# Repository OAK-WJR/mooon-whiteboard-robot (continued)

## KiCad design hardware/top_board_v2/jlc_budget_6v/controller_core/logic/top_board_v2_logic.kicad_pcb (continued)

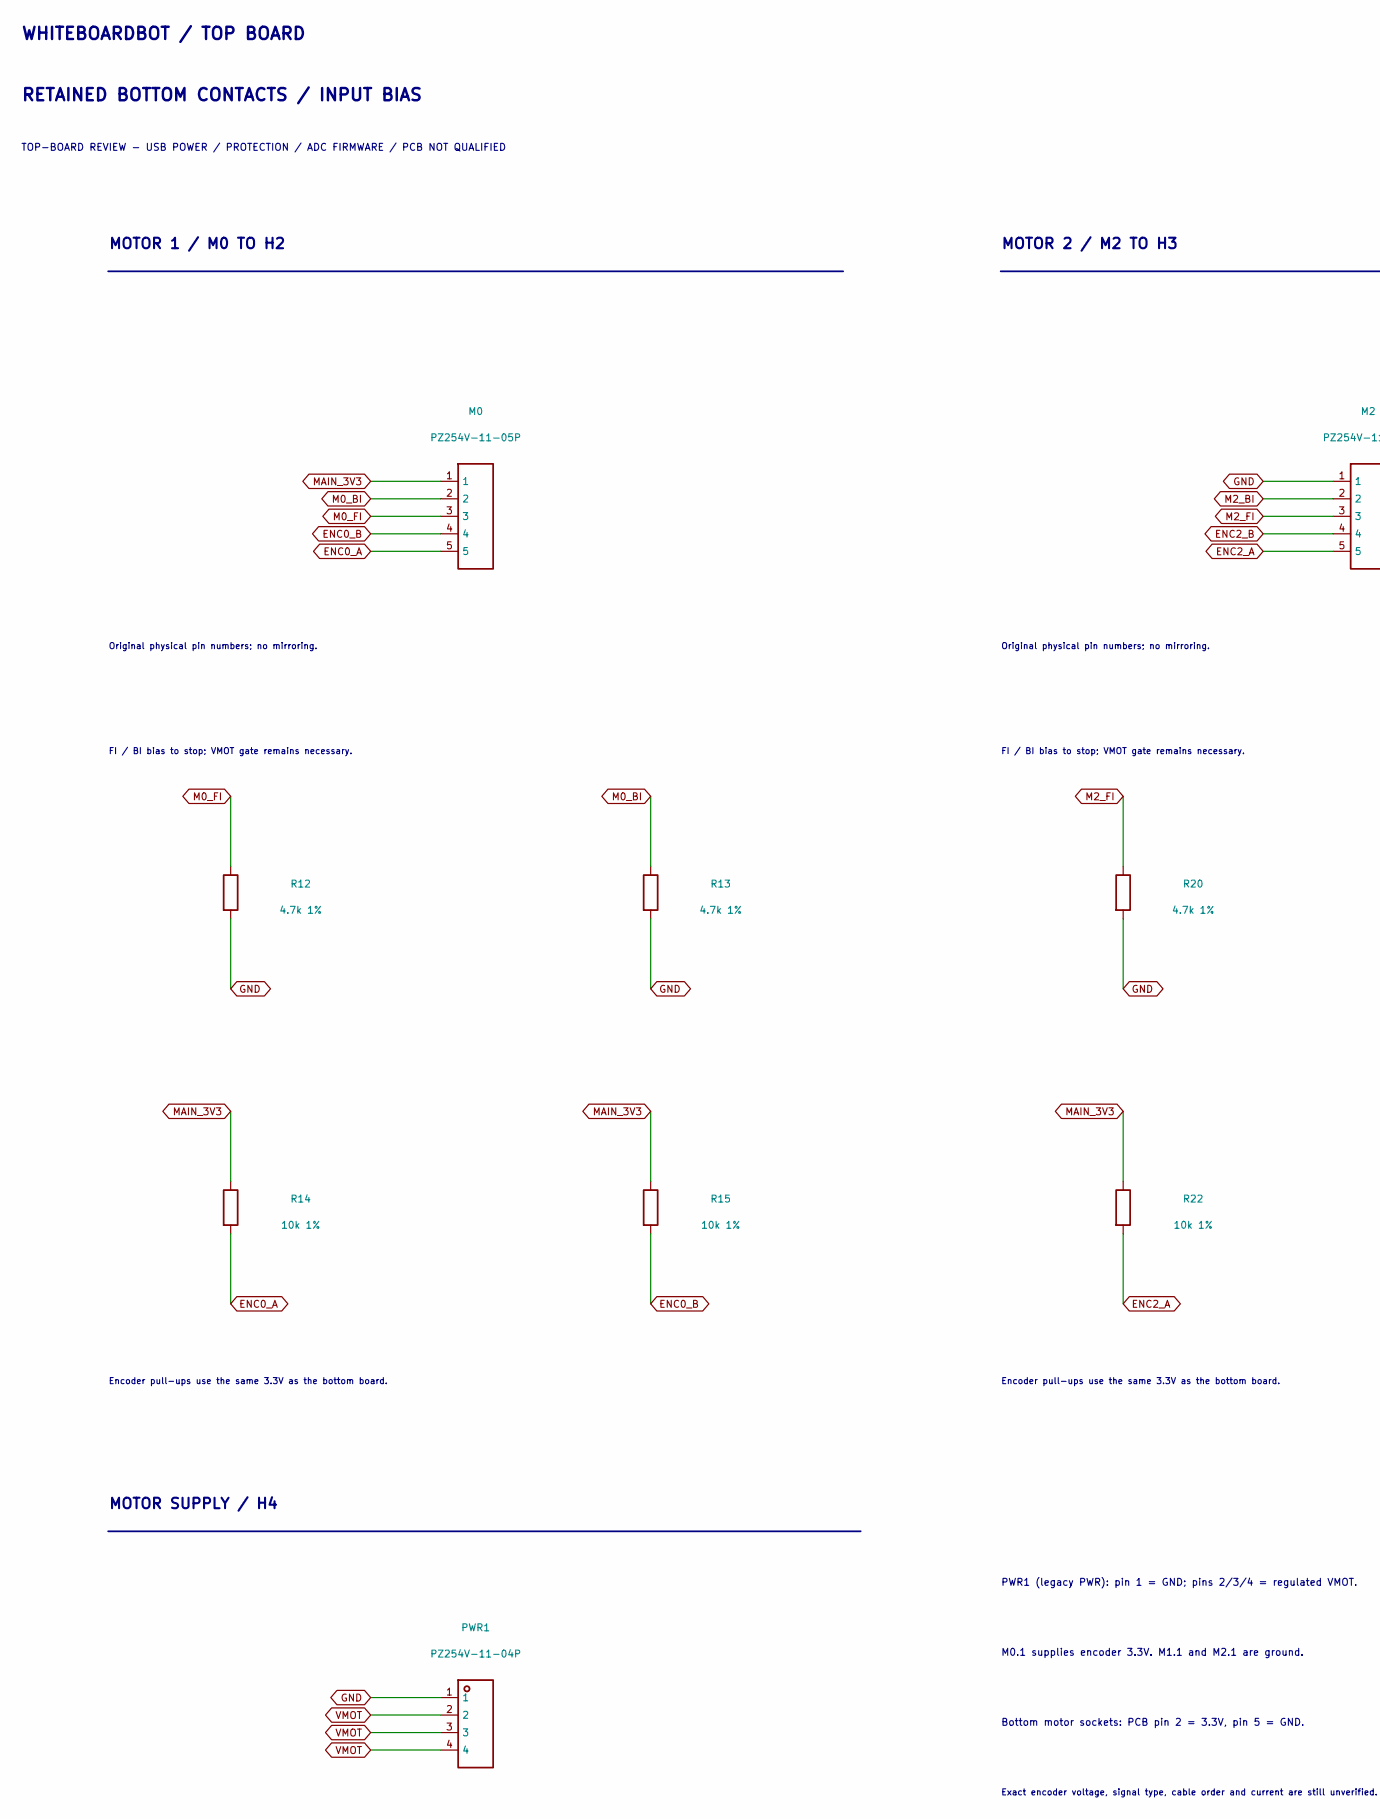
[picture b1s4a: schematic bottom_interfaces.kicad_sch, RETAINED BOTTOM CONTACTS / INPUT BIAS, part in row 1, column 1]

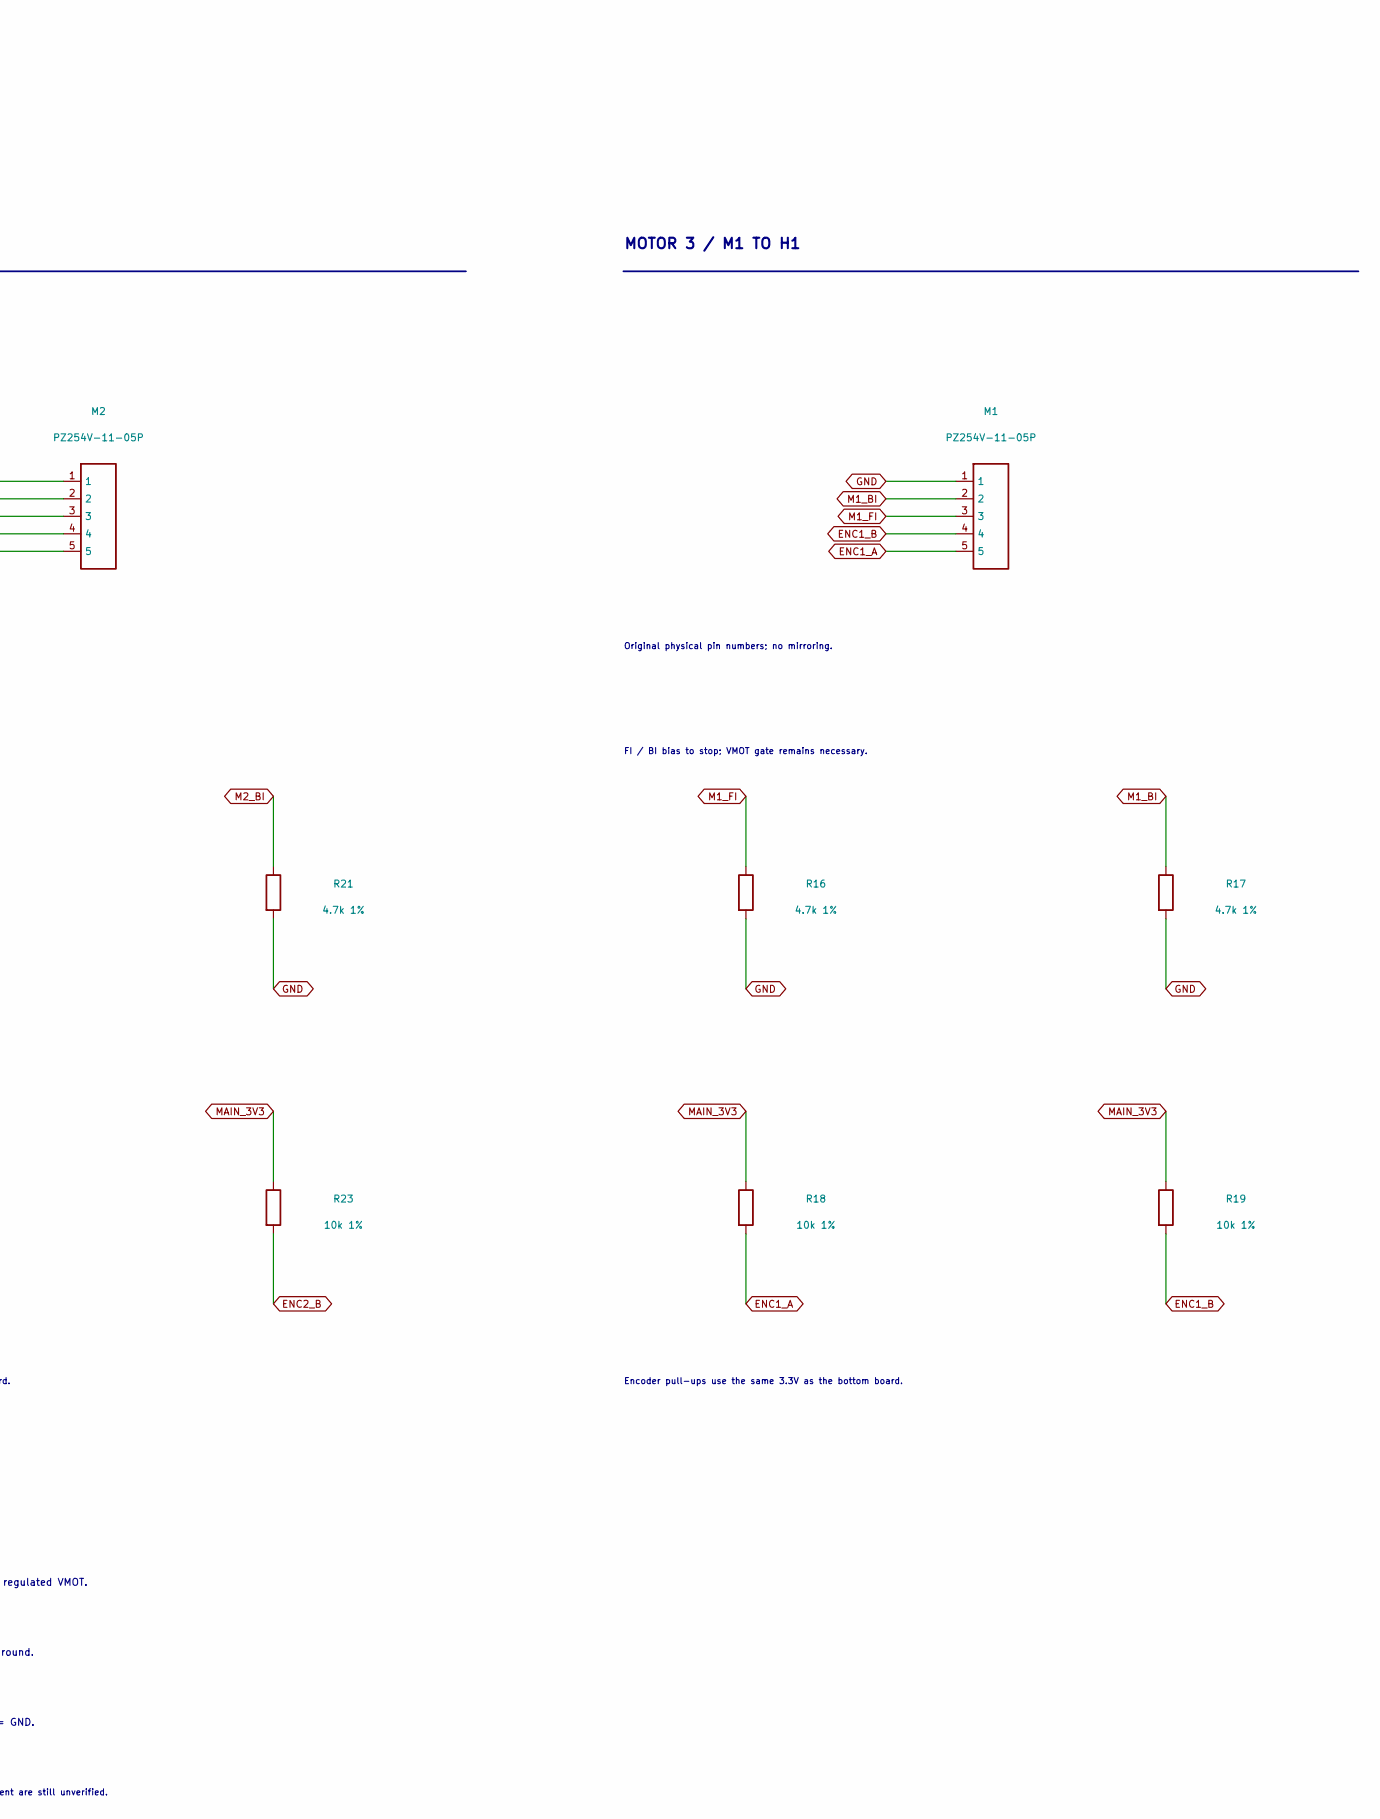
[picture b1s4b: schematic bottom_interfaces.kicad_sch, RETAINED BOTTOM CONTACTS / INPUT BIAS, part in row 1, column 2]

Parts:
M0: PZ254V-11-05P; M0_HDR-TH_5P-P2.54-V-M; LCSC C492404
M1: PZ254V-11-05P; M1_HDR-TH_5P-P2.54-V-M; LCSC C492404
M2: PZ254V-11-05P; M2_HDR-TH_5P-P2.54-V-M; LCSC C492404
PWR1: PZ254V-11-04P; PWR_HDR-TH_4P-P2.54-V-M; LCSC C2691448
R12, R13, R16, R17, R20, R21: 4.7k 1%; R_0603_1608Metric; mpn 0603WAF4701T5E; LCSC C23162
R14, R15, R18, R19, R22, R23: 10k 1%; R_0603_1608Metric; mpn 0603WAF1002T5E; LCSC C25804

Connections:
ENC0_A: M0.5, R14.2; also elsewhere on the board
ENC0_B: M0.4, R15.2; also elsewhere on the board
ENC1_A: M1.5, R18.2; also elsewhere on the board
ENC1_B: M1.4, R19.2; also elsewhere on the board
ENC2_A: M2.5, R22.2; also elsewhere on the board
ENC2_B: M2.4, R23.2; also elsewhere on the board
GND: M1.1, M2.1, PWR1.1, R12.2, R13.2, R16.2, R17.2, R20.2, R21.2; also elsewhere on the board
M0_BI: M0.2, R13.1; also elsewhere on the board
M0_FI: M0.3, R12.1; also elsewhere on the board
M1_BI: M1.2, R17.1; also elsewhere on the board
M1_FI: M1.3, R16.1; also elsewhere on the board
M2_BI: M2.2, R21.1; also elsewhere on the board
M2_FI: M2.3, R20.1; also elsewhere on the board
MAIN_3V3: M0.1, R14.1, R15.1, R18.1, R19.1, R22.1, R23.1; also elsewhere on the board
VMOT: PWR1.2, PWR1.3, PWR1.4; also elsewhere on the board

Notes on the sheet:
WHITEBOARDBOT / TOP BOARD
RETAINED BOTTOM CONTACTS / INPUT BIAS
TOP-BOARD REVIEW - USB POWER / PROTECTION / ADC FIRMWARE / PCB NOT QUALIFIED
MOTOR 1 / M0 TO H2
Original physical pin numbers; no mirroring.
FI / BI bias to stop; VMOT gate remains necessary.
Encoder pull-ups use the same 3.3V as the bottom board.
MOTOR 2 / M2 TO H3
MOTOR 3 / M1 TO H1
MOTOR SUPPLY / H4
PWR1 (legacy PWR): pin 1 = GND; pins 2/3/4 = regulated VMOT.
M0.1 supplies encoder 3.3V. M1.1 and M2.1 are ground.
Bottom motor sockets: PCB pin 2 = 3.3V, pin 5 = GND.
Exact encoder voltage, signal type, cable order and current are still unverified.

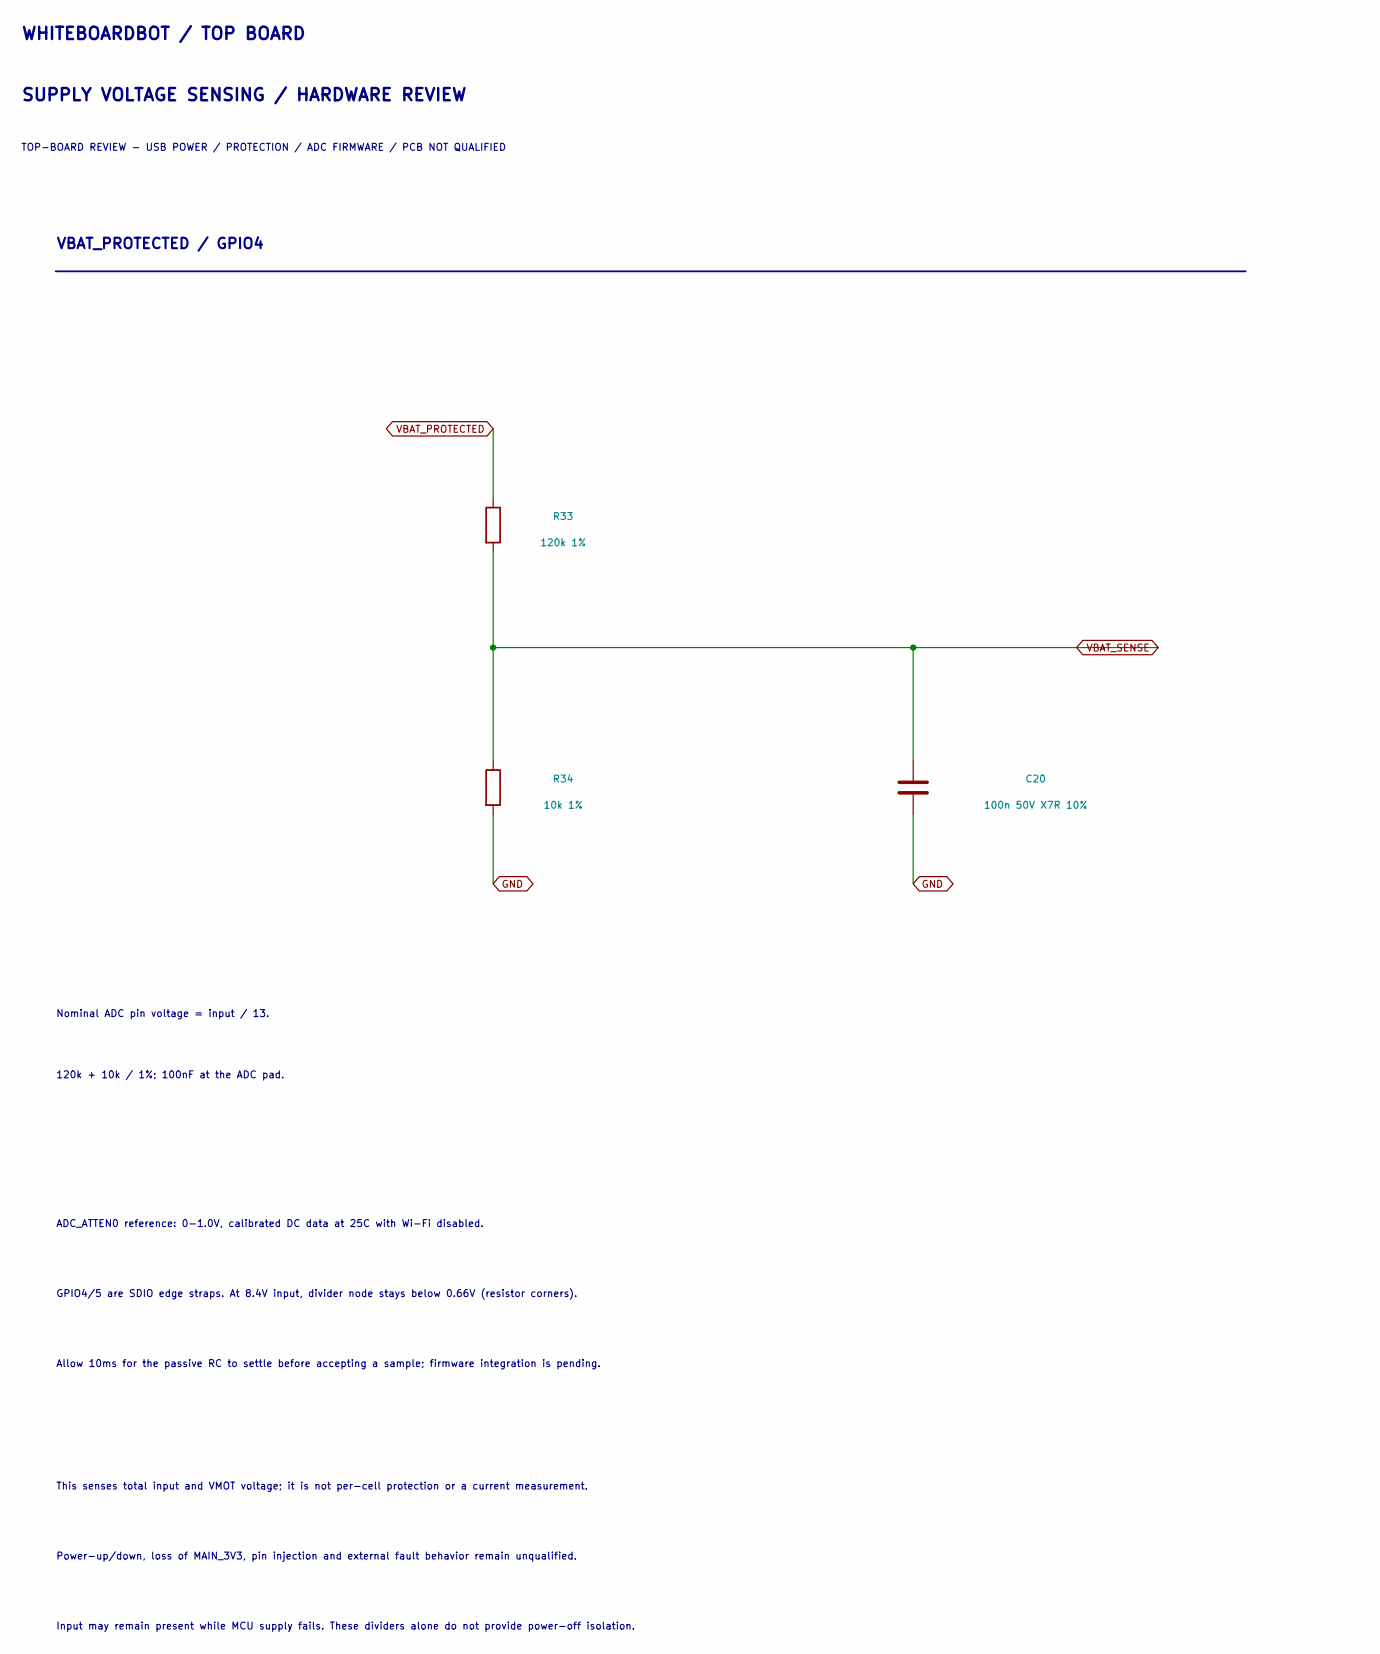
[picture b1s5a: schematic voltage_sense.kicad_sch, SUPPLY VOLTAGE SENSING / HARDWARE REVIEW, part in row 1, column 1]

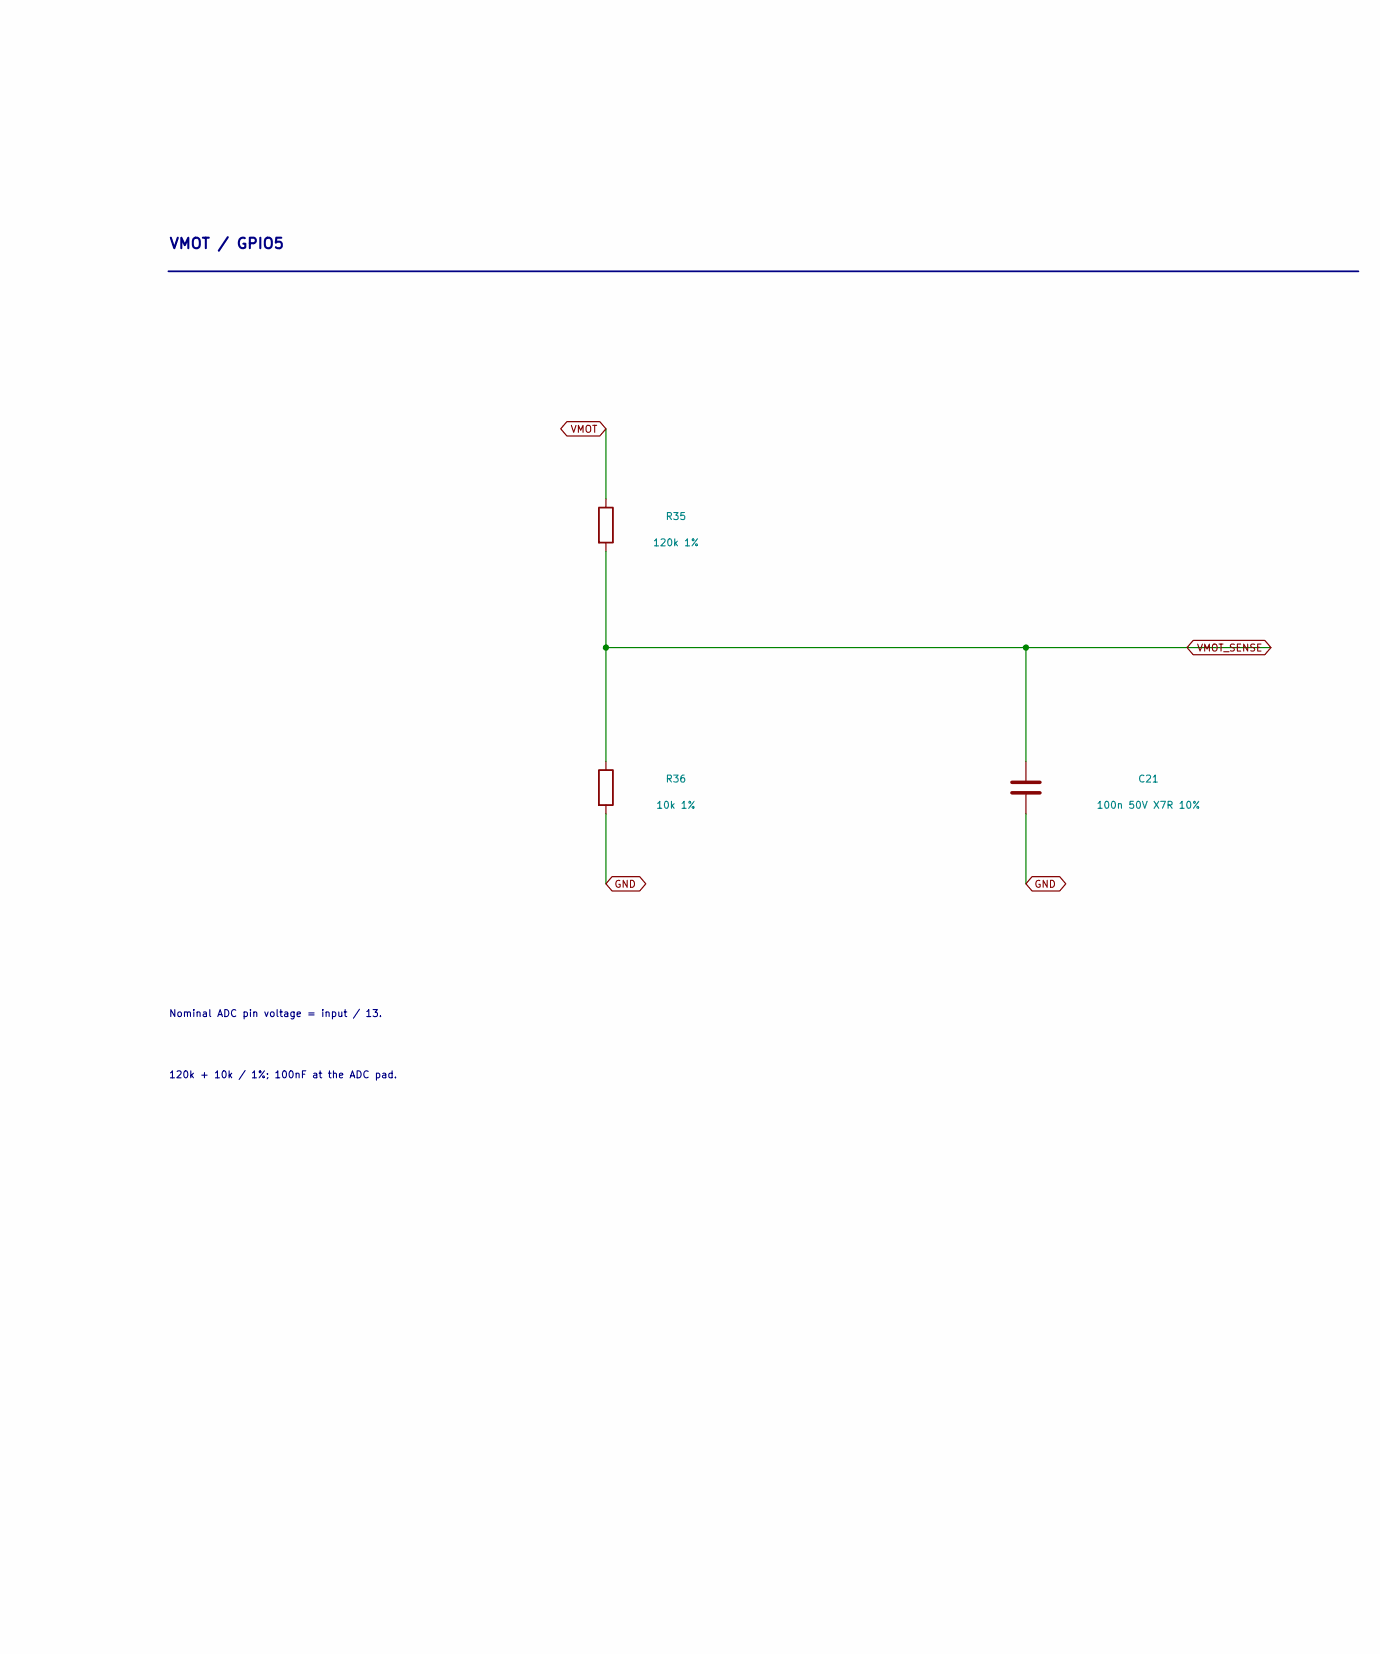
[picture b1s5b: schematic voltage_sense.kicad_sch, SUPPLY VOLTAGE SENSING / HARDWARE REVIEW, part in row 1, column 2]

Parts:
C20, C21: 100n 50V X7R 10%; C_0603_1608Metric; mpn CC0603KRX7R9BB104; LCSC C14663
R33, R35: 120k 1%; R_0603_1608Metric; mpn 0603WAF1203T5E; LCSC C25808
R34, R36: 10k 1%; R_0603_1608Metric; mpn 0603WAF1002T5E; LCSC C25804

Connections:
GND: C20.2, C21.2, R34.2, R36.2; also elsewhere on the board
VBAT_PROTECTED: R33.1; also elsewhere on the board
VBAT_SENSE: C20.1, R33.2, R34.1; also elsewhere on the board
VMOT: R35.1; also elsewhere on the board
VMOT_SENSE: C21.1, R35.2, R36.1; also elsewhere on the board

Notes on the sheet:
WHITEBOARDBOT / TOP BOARD
SUPPLY VOLTAGE SENSING / HARDWARE REVIEW
TOP-BOARD REVIEW - USB POWER / PROTECTION / ADC FIRMWARE / PCB NOT QUALIFIED
VBAT_PROTECTED / GPIO4
Nominal ADC pin voltage = input / 13.
120k + 10k / 1%; 100nF at the ADC pad.
VMOT / GPIO5
ADC_ATTEN0 reference: 0-1.0V, calibrated DC data at 25C with Wi-Fi disabled.
GPIO4/5 are SDIO edge straps. At 8.4V input, divider node stays below 0.66V (resistor corners).
Allow 10ms for the passive RC to settle before accepting a sample; firmware integration is pending.
This senses total input and VMOT voltage; it is not per-cell protection or a current measurement.
Power-up/down, loss of MAIN_3V3, pin injection and external fault behavior remain unqualified.
Input may remain present while MCU supply fails. These dividers alone do not provide power-off isolation.

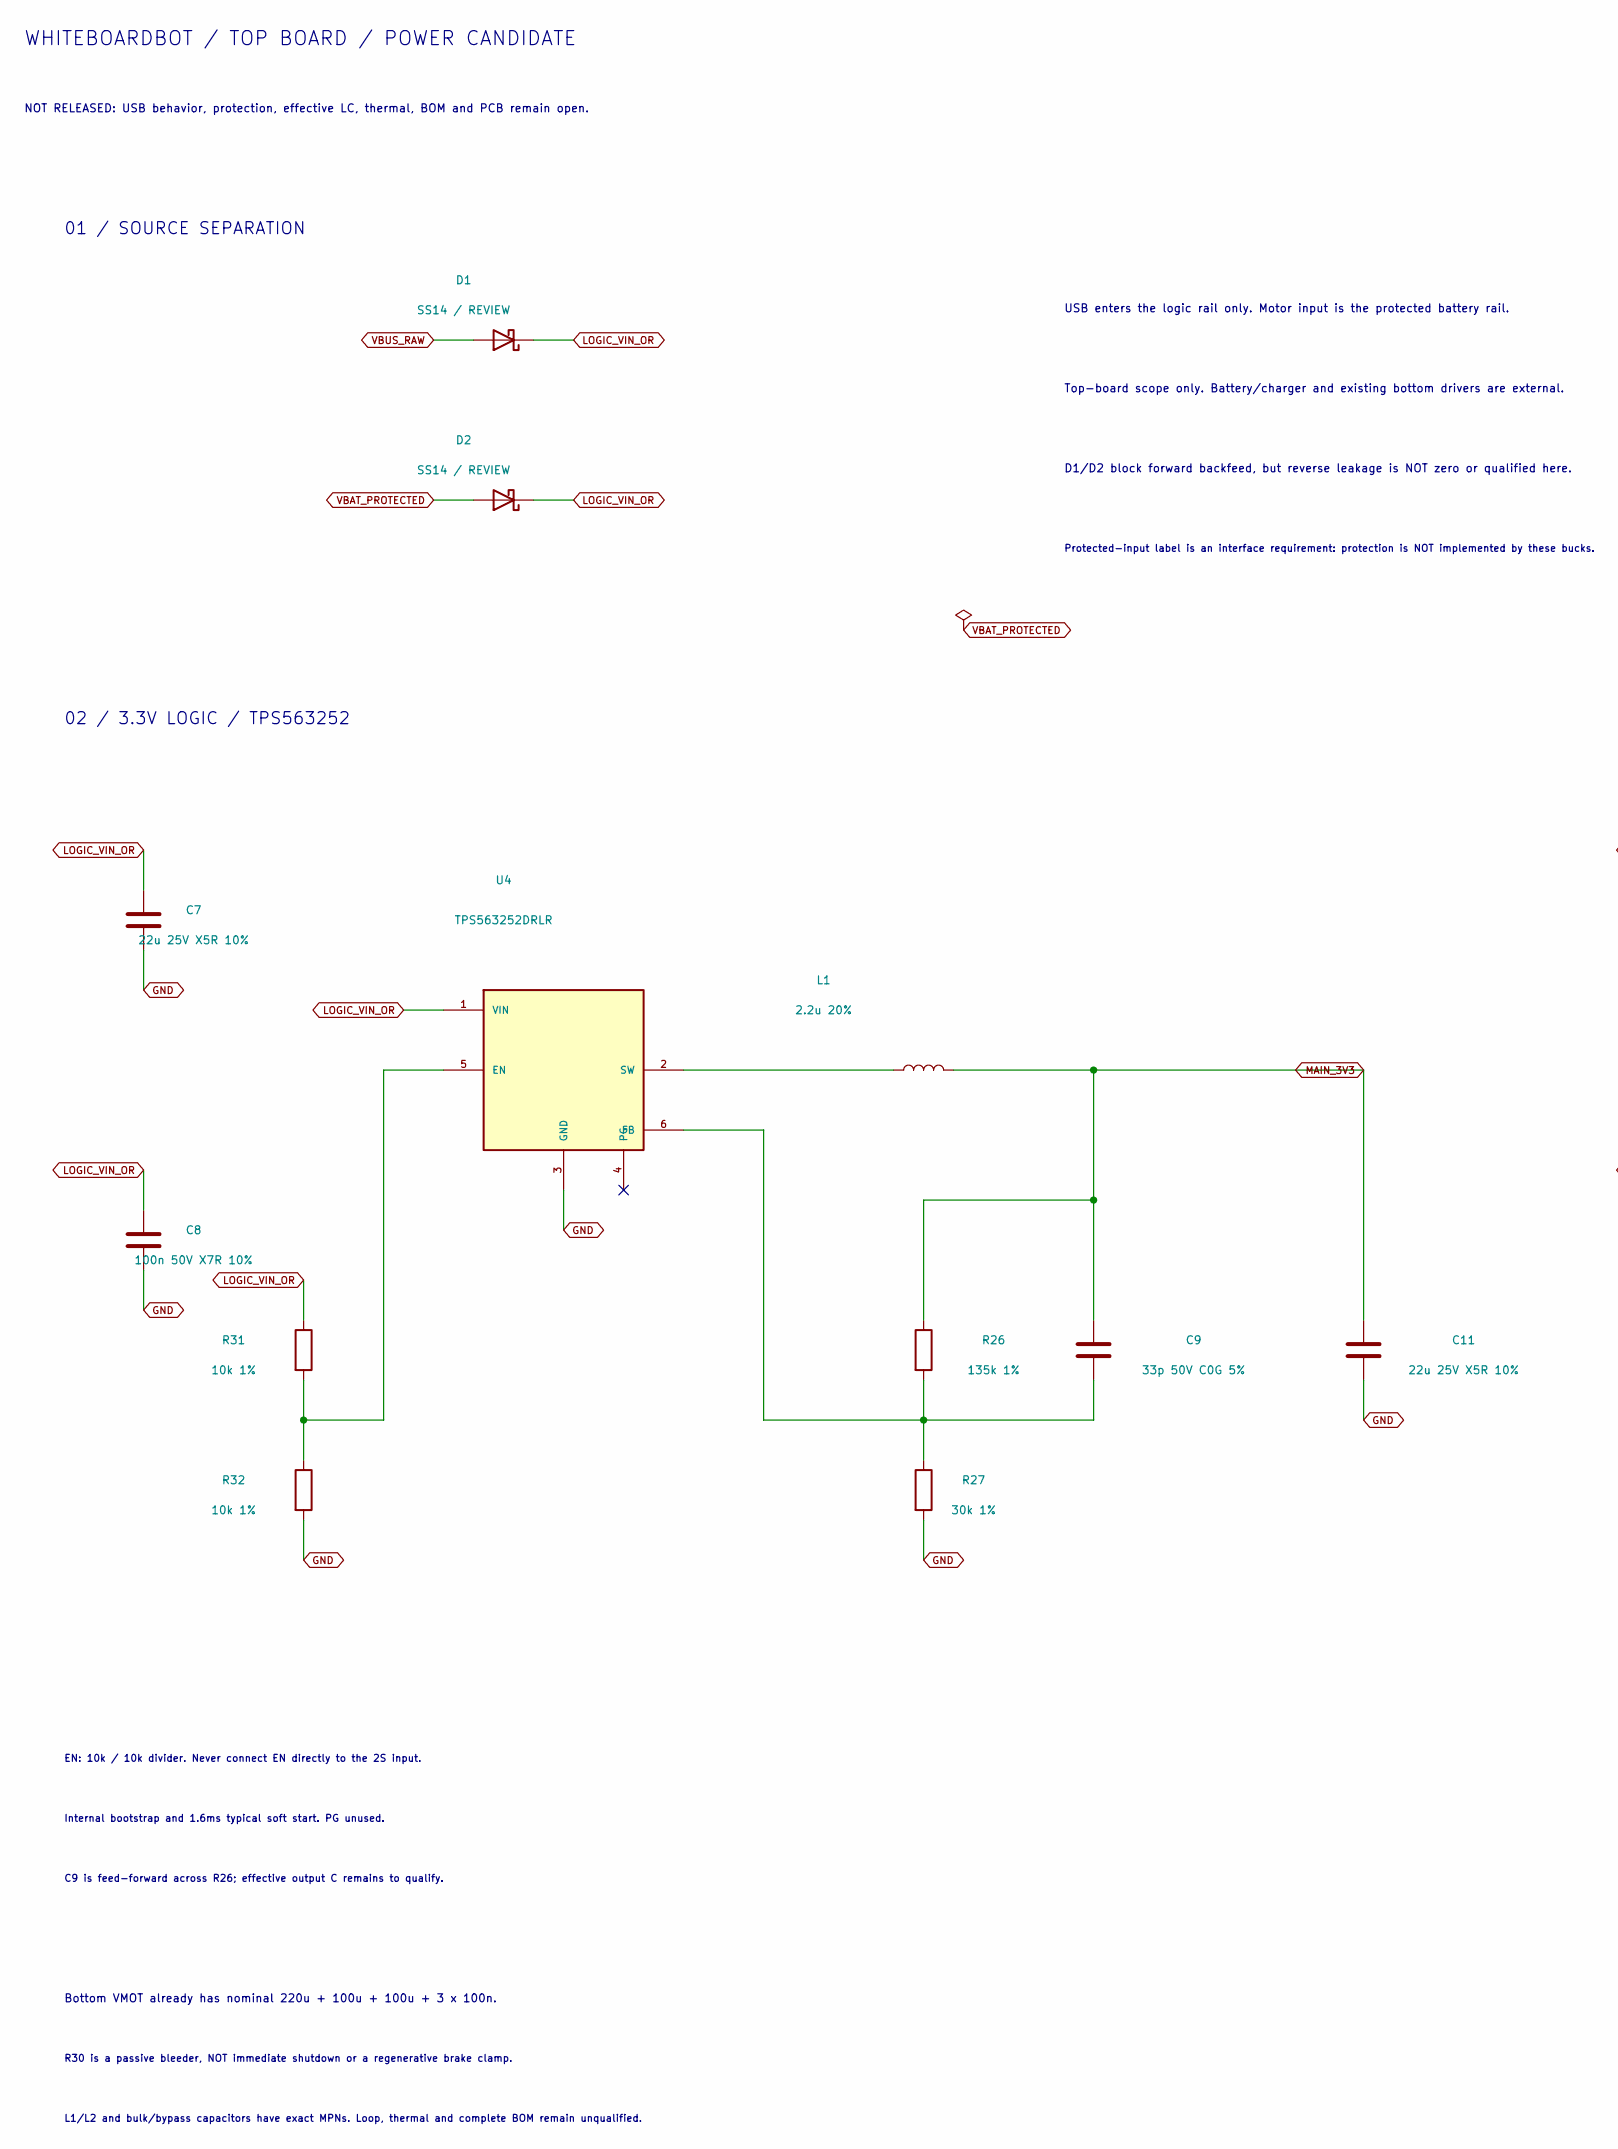
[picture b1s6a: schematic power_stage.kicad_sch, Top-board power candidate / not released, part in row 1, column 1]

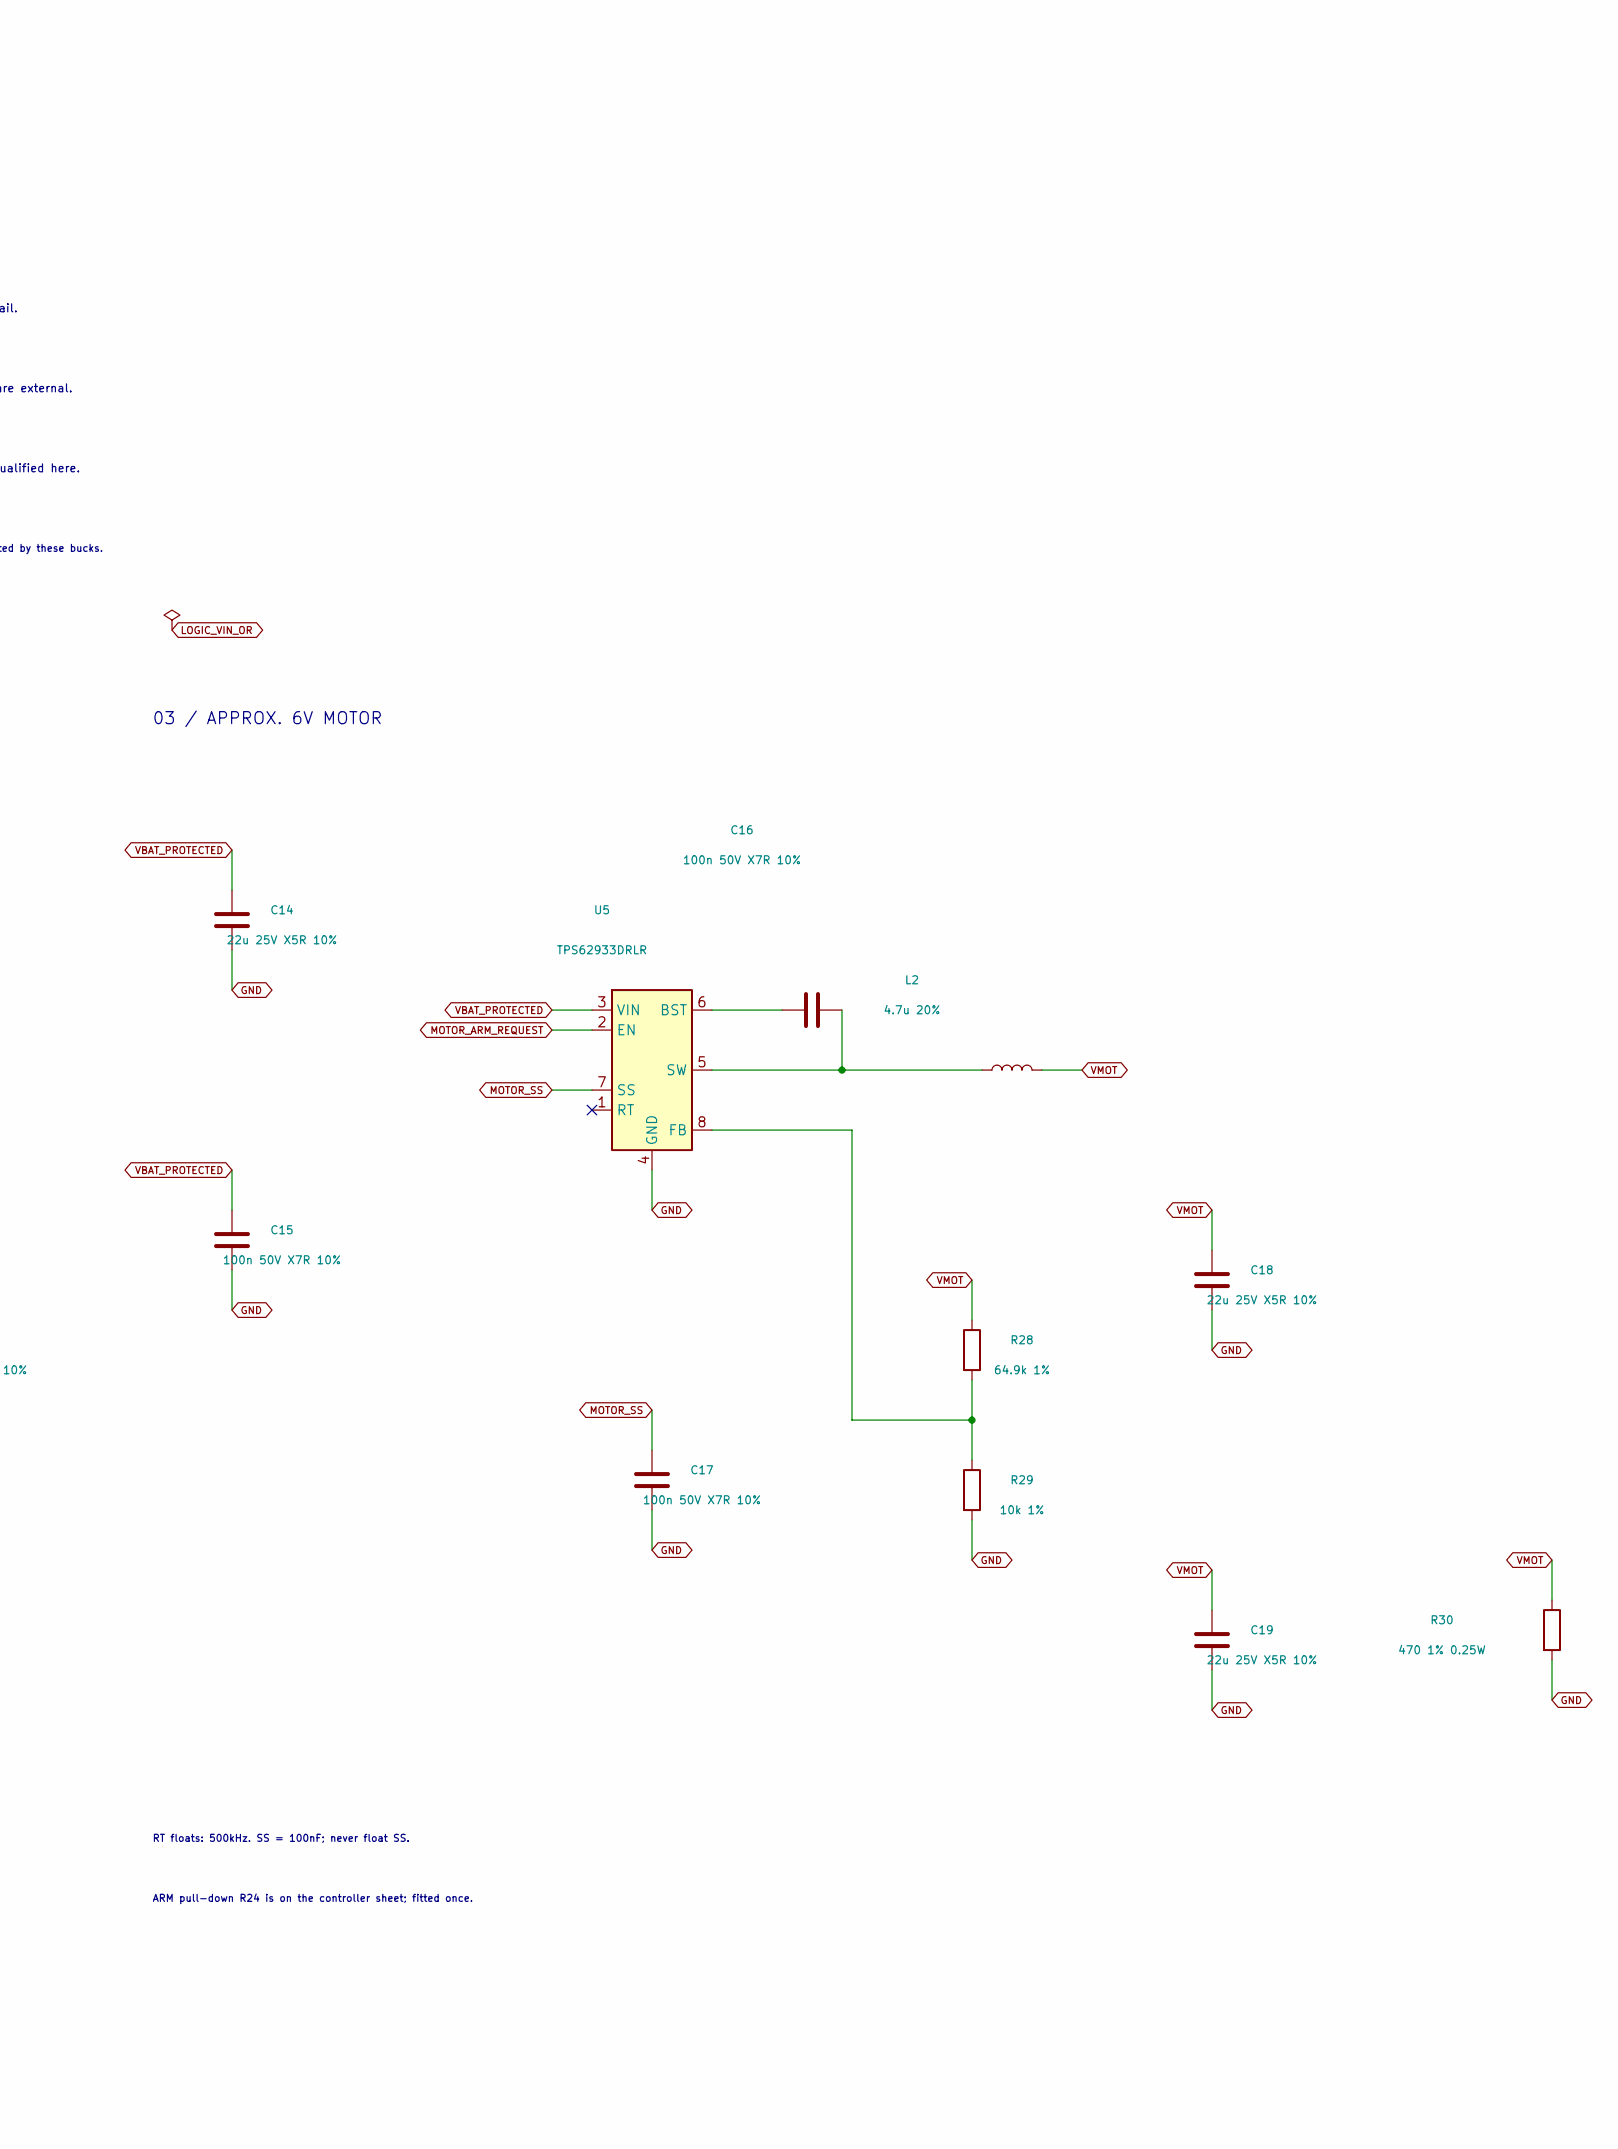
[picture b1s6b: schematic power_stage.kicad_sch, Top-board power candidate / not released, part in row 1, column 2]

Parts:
C7, C11, C14, C18, C19: 22u 25V X5R 10%; C_1206_3216Metric; mpn CL31A226KAHNNNE; LCSC C12891
C8, C15, C16, C17: 100n 50V X7R 10%; C_0603_1608Metric; mpn CC0603KRX7R9BB104; LCSC C14663
C9: 33p 50V C0G 5%; C_0603_1608Metric; mpn CL10C330JB8NNNC; LCSC C1663
D1, D2: SS14 / REVIEW; D_SMA; LCSC C2480
L1: 2.2u 20%; L_Sunlord_MWSA0603S; mpn MWSA0603S-2R2MT; LCSC C408445
L2: 4.7u 20%; L_Sunlord_MWSA0603S; mpn MWSA0603S-4R7MT; LCSC C408447
R26: 135k 1%; R_0603_1608Metric
R27: 30k 1%; R_0603_1608Metric; mpn 0603WAF3002T5E; LCSC C22984
R28: 64.9k 1%; R_0603_1608Metric; mpn 0603WAF6492T5E; LCSC C14891
R29, R31, R32: 10k 1%; R_0603_1608Metric; mpn 0603WAF1002T5E; LCSC C25804
R30: 470 1% 0.25W; R_1206_3216Metric
U4: TPS563252DRLR; SOT-563; LCSC C19188399
U5: TPS62933DRLR; SOT-583-8; LCSC C3200405

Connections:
GND: C7.2, C8.2, C11.2, C14.2, C15.2, C17.2, C18.2, C19.2, R27.2, R29.2, R30.2, R32.2, U4.3 (GND), U5.4 (GND); also elsewhere on the board
LOGIC_VIN_OR: C7.1, C8.1, D1.1 (K), D2.1 (K), R31.1, U4.1 (VIN)
MAIN_3V3: C9.1, C11.1, L1.2, R26.1; also elsewhere on the board
MOTOR_ARM_REQUEST: U5.2 (EN); also elsewhere on the board
MOTOR_SS: C17.1, U5.7 (SS)
unnamed: R31.2, R32.1, U4.5 (EN)
unnamed: C9.2, R26.2, R27.1, U4.6 (FB)
unnamed: L1.1, U4.2 (SW)
unnamed: C16.1, U5.6 (BST)
unnamed: R28.2, R29.1, U5.8 (FB)
unnamed: C16.2, L2.1, U5.5 (SW)
VBAT_PROTECTED: C14.1, C15.1, D2.2 (A), U5.3 (VIN); also elsewhere on the board
VBUS_RAW: D1.2 (A); also elsewhere on the board
VMOT: C18.1, C19.1, L2.2, R28.1, R30.1; also elsewhere on the board

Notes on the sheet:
WHITEBOARDBOT / TOP BOARD / POWER CANDIDATE
NOT RELEASED: USB behavior, protection, effective LC, thermal, BOM and PCB remain open.
01 / SOURCE SEPARATION
USB enters the logic rail only. Motor input is the protected battery rail.
Top-board scope only. Battery/charger and existing bottom drivers are external.
D1/D2 block forward backfeed, but reverse leakage is NOT zero or qualified here.
Protected-input label is an interface requirement: protection is NOT implemented by these bucks.
02 / 3.3V LOGIC / TPS563252
EN: 10k / 10k divider. Never connect EN directly to the 2S input.
Internal bootstrap and 1.6ms typical soft start. PG unused.
C9 is feed-forward across R26; effective output C remains to qualify.
03 / APPROX. 6V MOTOR
RT floats: 500kHz. SS = 100nF; never float SS.
ARM pull-down R24 is on the controller sheet; fitted once.
Bottom VMOT already has nominal 220u + 100u + 100u + 3 x 100n.
R30 is a passive bleeder, NOT immediate shutdown or a regenerative brake clamp.
L1/L2 and bulk/bypass capacitors have exact MPNs. Loop, thermal and complete BOM remain unqualified.
